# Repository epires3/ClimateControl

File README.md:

# ECE 388 Embedded Design Climate Control Project
## Hardware
* ATMega328p
* DHT-22 Temp Sensor
* 2x IR Sensor
* (See BOM for all board components)
## Team
* Eric Pires
* Richard Harrison
* John Lamanuzzi

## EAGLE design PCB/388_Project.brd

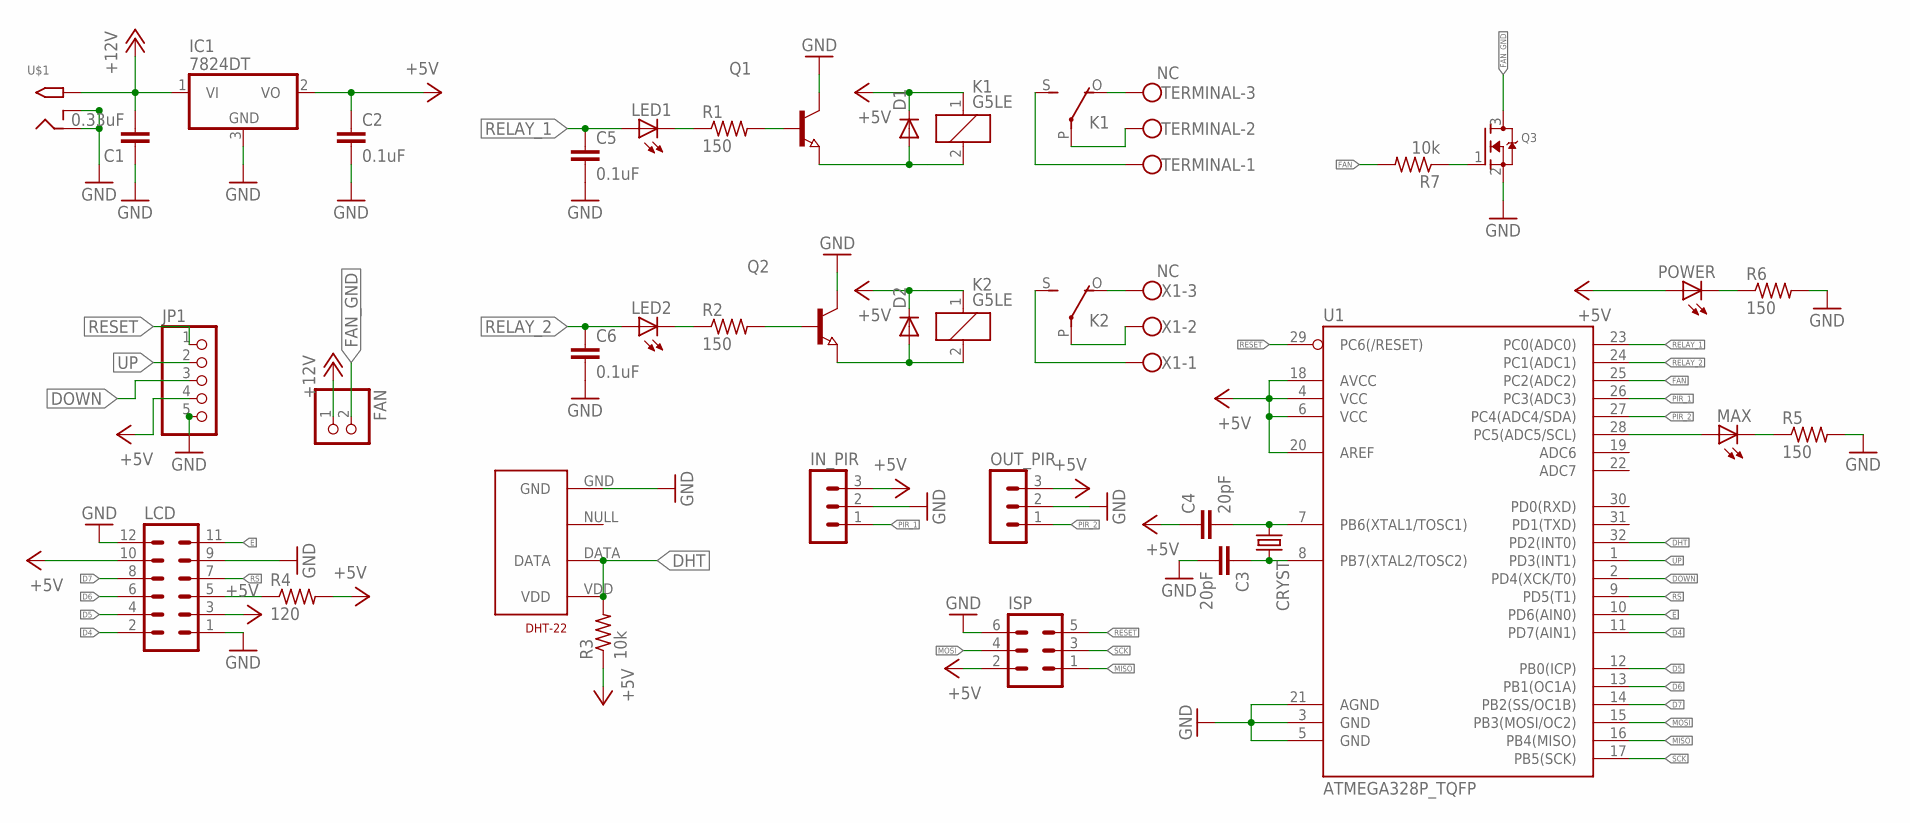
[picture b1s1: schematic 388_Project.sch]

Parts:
C1: 0.33uF; 0805
C2, C5, C6: 0.1uF; 0805
C3, C4: 20pF; 0805
CRYST: CRYSTALHC49UP; HC49UP
D1, D2: DIODE-DO-214AC; DO-214AC
DHT-22: RHT03_DHT-22_AM2302RA; RHT03_DHT-22/RA
FAN: JST_2PIN-SMT; JST-PH-2-SMT
IC1: 7824DT; TO252
IN_PIR: MA03-1
ISP: MA03-2
JP1: PINHD-1X5; 1X05
K1, K2: G5LE
LCD: MA06-2
LED1, LED2: LEDSML0805; SML0805
MAX: LEDSML0805; SML0805
OUT_PIR: MA03-1
POWER: LEDSML0805; SML0805
Q1, Q2: NPN-TRANSISTOR_SOT23; SOT23
Q3: MOSFET-NREFLOW; SOT23
R1, R2, R5, R6: 150; M0805
R3, R7: 10k; M0805
R4: 120; M0805
TERMINAL: NC; W237-103
U1: ATMEGA328P_TQFP; TQFP32-08
U$1: 2.1MMJACKTHM; PJ-102A
X1: NC; W237-103

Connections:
+5V: C2.1, C4.1, D1.C, D2.C, IC1.2 (VO), IN_PIR.3, ISP.2, JP1.4, K1.1, K2.1, LCD.3, LCD.10, OUT_PIR.3, POWER.A, R3.1, R4.2, U1.4 (VCC), U1.6 (VCC), U1.18 (AVCC), U1.20 (AREF)
+12V: C1.2, FAN.1 (2), IC1.1 (VI), U$1.TIP
D4: LCD.2, U1.11 (PD7(AIN1))
D5: LCD.4, U1.12 (PB0(ICP))
D6: LCD.6, U1.13 (PB1(OC1A))
D7: LCD.8, U1.14 (PB2(SS/OC1B))
DHT: DHT-22.DATA, DHT-22.VDD, R3.2, U1.32 (PD2(INT0))
DOWN: JP1.3, U1.2 (PD4(XCK/T0))
E: LCD.11, U1.10 (PD6(AIN0))
FAN: R7.2, U1.25 (PC2(ADC2))
FAN_GND: FAN.2 (1), Q3.3 (D)
GND: C1.1, C2.2, C3.2, C5.2, C6.2, DHT-22.GND, IC1.3 (GND), IN_PIR.2, ISP.6, JP1.5, LCD.1, LCD.9, LCD.12, OUT_PIR.2, Q1.3 (C), Q2.3 (C), Q3.2 (S), R5.2, R6.2, U1.3 (GND), U1.5 (GND), U1.21 (AGND), U$1.RING, U$1.RING_SW
MISO: ISP.1, U1.16 (PB4(MISO))
MOSI: ISP.4, U1.15 (PB3(MOSI/OC2))
unnamed: K1.O, TERMINAL.3
unnamed: Q3.1 (G), R7.1
unnamed: C3.1, CRYST.2, U1.8 (PB7(XTAL2/TOSC2))
unnamed: C4.2, CRYST.1, U1.7 (PB6(XTAL1/TOSC1))
unnamed: K1.S, TERMINAL.1
unnamed: K1.P, TERMINAL.2
unnamed: LED1.C, R1.1
unnamed: LED2.C, R2.1
unnamed: Q1.1 (B), R1.2
unnamed: Q2.1 (B), R2.2
unnamed: D1.A, K1.2, Q1.2 (E)
unnamed: D2.A, K2.2, Q2.2 (E)
unnamed: MAX.A, U1.28 (PC5(ADC5/SCL))
unnamed: MAX.C, R5.1
unnamed: POWER.C, R6.1
unnamed: K2.O, X1.3
unnamed: K2.S, X1.1
unnamed: K2.P, X1.2
unnamed: LCD.5, R4.1
PIR_1: IN_PIR.1, U1.26 (PC3(ADC3))
PIR_2: OUT_PIR.1, U1.27 (PC4(ADC4/SDA))
RELAY_1: C5.1, LED1.A, U1.23 (PC0(ADC0))
RELAY_2: C6.1, LED2.A, U1.24 (PC1(ADC1))
RESET: ISP.5, JP1.1, U1.29 (PC6(/RESET))
RS: LCD.7, U1.9 (PD5(T1))
SCK: ISP.3, U1.17 (PB5(SCK))
UP: JP1.2, U1.1 (PD3(INT1))

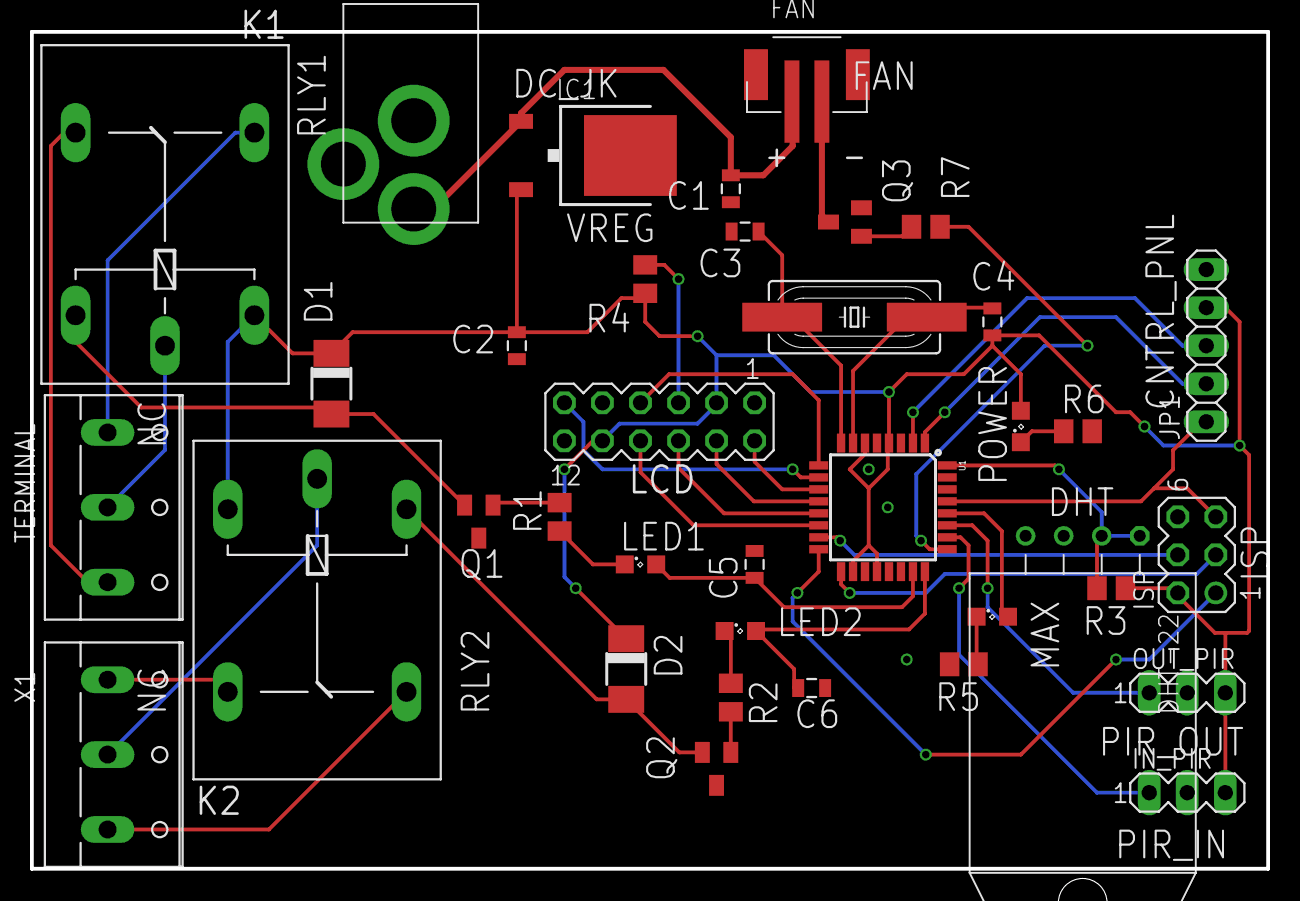
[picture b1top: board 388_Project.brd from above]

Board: 2 copper layers, 82.5 x 55.9 mm, 37 parts (0 on the bottom side), 41 nets.

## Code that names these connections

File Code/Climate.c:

/*
 * ECE388Climate.c
 *
 * Created: 11/17/2016 10:50:30 PM
 * Author : Johnny
 */ 

#ifndef F_CPU
#define F_CPU 16000000UL 
#endif


#define D4 PD7
#define D5 PB0
#define D6 PB1
#define D7 PB2
#define RS PD5
#define E PD6

#define DHT PD2

#define UP PD3
#define DOWN PD4

#define PIR1 PC3
#define PIR2 PC4

#define LED PC5

#define FAN PC2

#define RELAY1 PC0
#define RELAY2 PC1

#include <avr/io.h>
#include <util/delay.h>
#include <avr/interrupt.h>

unsigned int roomCount; 

unsigned int current_temp = 0;
unsigned int humidity = 0;
unsigned int set_temp;

int main(void)
{
    
	DDRD = 0xff;
	DDRC = 0xff;

	//PIR ISR
	DDRC &= ~(1<<DDC3); //PIR 1
	DDRC &= ~(1<<DDC4); //PIR 2
	PCMSK1 |= 1<<PCINT11 | 1<<PCINT22;
	PCICR |= 1<<PCIE1;

	sei();	

    while (1) 
    {
		
		//Max Capacity - Enable LED
		if (roomCount > 5)
		PORTC |= (1<<LED);
		//OK Capacity - Ensure LED is off
		if (roomCount < 5)
		PORTC |= (0<<LED);
		//If roomCount goes negative, it is reset to 0
		if (roomCount < 0)
		roomCount = 0; 
		//Enable Relay 1
		if (roomCount < 1)
		PORTC |= (1<<RELAY1);
		//Disable Relay 1 
		if (roomCount < 1)
		PORTC |= (0<<RELAY1);

    }
	
}

ISR(PCINT1_vect)
{
	if(PIR1 == 0)
	{
		if(PIR2 == 0){
			roomCount++;
			PORTC |= (0<<PIR2);
		}
	}
	
	else
	{
		if(PIR2 == 0)
			PORTC |= (1<<PIR2);
	}
}

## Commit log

2016-09-17 Design Outline
2016-09-20 Create foo
2016-09-20 Lab Photos
2016-09-20 Create Labs
2016-09-20 test.txt
2016-09-20 Procedures, Results & Reflection
2016-09-21 Final Report
2016-09-21 Final Draft
2016-09-25 Microcontroller and Character LCD
2016-09-25 Temp Sensor, Fans & LEDs
2016-09-26 Added Basic Design Graphic
2016-10-11 Prototype Code and Procedures
2016-10-31 PCB Rev 1
    Traces for relay need adjustments, button breakout board still required
2016-11-23 LCD Functionality
2017-02-01 Lab Template
2017-08-15 Removed Labs Folder, Moved to Deliverables

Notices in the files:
parts and their libraries:
SparkFun-Capacitors: Licensing: Creative Commons ShareAlike 4.0 International - https://creativecommons.org/licenses/by-sa/4.0
